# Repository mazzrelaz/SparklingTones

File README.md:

# SparklingTones

*Italiano · [English](README.en.md)*

App personale per controllare e organizzare i preset di un **Positive Grid Spark 2**
via Bluetooth, dal browser. Più un pedale ESP32 che fa lo stesso col piede.

**→ [mazzrelaz.github.io/SparklingTones](https://mazzrelaz.github.io/SparklingTones/)** · [guida all'uso](https://mazzrelaz.github.io/SparklingTones/guida.html)
(anche dentro l'app: menu ⋯ → Guida)

> **Progetto personale, in pausa.** È nato per risolvere un problema mio e funziona
> sul mio ampli. Il protocollo dello Spark 2 non è documentato da nessuna parte: qui
> è stato ricostruito osservando, misurando e verificando sull'hardware. Se stai
> cercando quello, la parte che ti serve è in [`docs/`](docs/) — vedi in fondo.

L'app è in italiano e in inglese (la lingua si sceglie nel pannello «Altro»). La
documentazione tecnica è in italiano, tranne il protocollo, che c'è anche
[in inglese](docs/protocollo-spark2.en.md).

---

## Cosa fa

**Organizza la libreria.** Lo Spark 2 tiene otto preset alla volta; l'app tiene tutti
quelli che vuoi, con nome, categorie, note e famiglia di suono, in un database nel
browser. Legge i preset dall'ampli, importa il `preset_backup.zip` dell'app ufficiale,
esporta e reimporta in JSON.

**Suona.** Una vista *Live* con banchi da otto pulsantoni grandi, pensata per essere
usata mentre si suona invece che per catalogare. Un preset già caricato sull'ampli si
attiva all'istante; uno che non c'è viene trasmesso per intero in circa un secondo.

**Regola.** Un editor della catena effetti che agisce **sul suono che sta suonando**:
le manopole si muovono e l'ampli risponde. Legge sempre lo stato vero dall'ampli prima
di aprirsi, perché la verità è lì e non nella libreria.

**Funziona senza rete.** È una PWA: installata, si apre e funziona anche offline —
a un concerto la rete non c'è.

## Cosa serve

Un browser con **Web Bluetooth**: Chrome o Edge su computer e Android.
**Su iPhone e iPad serve Bluefy** («Bluefy – Web BLE Browser» nell'App Store),
un browser gratuito che Web Bluetooth ce l'ha: Safari e gli altri no, perché su iOS ogni
browser è obbligato a usare il motore di Apple. Provato su iPhone e iPad: va tutto.
La libreria che sta in Safari non passa da sola in Bluefy: si esporta e si reimporta.

Niente altro. Niente account, niente server: la libreria sta nel tuo browser e non
esce di lì.

## Farlo girare

Non c'è niente da compilare e niente da installare.

```
git clone https://github.com/mazzrelaz/SparklingTones.git
```

Poi apri `index.html` con un doppio clic. Funziona da `file://` — per questo i moduli
sono classic script e non ES module.

Attenzione a una cosa: `file://` e `https://` sono **due origini diverse**, quindi due
database diversi. La libreria non passa dall'una all'altra da sola: si esporta in JSON
e si reimporta.

## Il pedale

In [`pedale/`](pedale/) c'è il firmware per un **ESP32-C3**: prende i banchi dall'app
via Bluetooth, se li tiene in memoria e poi è autonomo — si collega da solo all'ampli
e cambia preset col piede, senza telefono.

Verificato sull'hardware, su una schedina nuda senza saldature:

| | misurato |
|---|---|
| un preset intero, intervallo di connessione di sistema | 1246 ms |
| lo stesso, chiedendo 7,5 ms | **326 ms** |
| a regime | **178–215 ms** |

Il secondo che ci mette il telefono non è banda: sono sedici round-trip BLE. Web
Bluetooth non lascia toccare l'intervallo di connessione, NimBLE sull'ESP32 sì, ed è
tutta la differenza.

**Il firmware non serializza niente.** L'app produce i frame già pronti e il pedale
corregge un byte solo — il sequence number, che il checksum non copre. L'encoder resta
uno solo, in JavaScript, coperto dai test.

Il pedale è a metà: funziona su una devkit, l'hardware vero (cinque footswitch, due
tasti, LED, display) non è ancora stato costruito. `tools/pedale-sim.html` ne simula la
faccia in una pagina, con dentro la logica vera.

## Il protocollo — la parte utile a qualcun altro

Questa è probabilmente la ragione per cui sei qui. Tutto in
**[`docs/protocollo-spark2.md`](docs/protocollo-spark2.md)**, e le trappole più costose
sono riassunte in [`CLAUDE.md`](CLAUDE.md).

GATT: service `0xFFC0`, write `0xFFC1` (solo *write without response*), notify `0xFFC2`.
Messaggi `F0 01 <seq> <checksum> <cmd> <sub> <dati impacchettati> F7`, con i dati
codificati 7/8 bit e i float in big endian.

Quello che è costato di più scoprire:

- **I comandi sugli effetti vogliono un byte `0x00` in coda.** Senza, l'ampli risponde
  con un ack regolare e **non applica il comando**. Non è documentato da nessuna fonte,
  ed è una differenza dello Spark 2.
- **Chunk da 25 byte, non 128.** Con 128 lo Spark 2 si disconnette.
- **Tutti i chunk di un preset vanno con lo stesso sequence number**, altrimenti l'ampli
  li conferma tutti senza assemblarne nessuno.
- **`0x0127` non salva sullo Spark 2**, in nessuna delle forme provate.
- **Far suonare un preset e salvarlo in uno slot sono due strade diverse**, e la seconda
  vuole un giro via-e-ritorno che sembra decorazione e non lo è.
- **L'ack conferma la ricezione, non l'esecuzione.** E `writeWithoutResponse` fa sembrare
  riuscita ogni scrittura: l'assenza di errori non è una verifica.

Il looper si comanda (`0x0175`), tranne la battuta di conteggio col click: quella è
un'indagine chiusa, e tutto ciò che è stato escluso sta in
[`docs/looper.md`](docs/looper.md), così nessuno ripercorre sette strade già chiuse.

Le catture grezze dall'ampli sono in [`captures/`](captures/).

## Test

Aprire le pagine in `test/`. Girano contro catture reali dell'ampli, quindi
intercettano una regressione nella codifica senza avere l'hardware a portata.

| | |
|---|---|
| `protocol-test.html` | 125 test — encoder e decoder, round-trip byte per byte |
| `transport-test.html` | 48 test — coda di invio e riassemblaggio |
| `store-test.html` | 99 test — libreria, banchi, categorie |
| `backup-test.html` | 33 test — lettura dello zip dell'app ufficiale |

## Avvertenze

**Scrivere in uno slot dell'ampli non si torna indietro.** Quello che c'era prima è
perso.

**L'ampli si può piantare**, e allora serve staccare la corrente. Succede coi comandi
pesanti — ricostruire un blocco DSP, o girare le manopole più in fretta di quanto la
radio riesca a portare.

**L'elenco dei modelli di effetto non è verificato**: viene da un catalogo di terzi, e
chiedere all'ampli un modello che non ha è uno dei modi per piantarlo. L'app distingue
quelli che ha visto uscire dal tuo ampli da quelli solo supposti.

**Provato su un solo Spark 2.** Con un altro esemplare, o un altro firmware, non so
cosa succede.

## Licenza e riconoscimenti

MIT, Massimo Togni. Vedi [`LICENSE`](LICENSE) e [`NOTICE`](NOTICE).

- I nomi di effetti e manopole vengono dal catalogo di
  **[Soundshed](https://github.com/soundshed/soundshed-app)** (MIT).
- Il riferimento per il protocollo BLE è
  **[paulhamsh/Spark](https://github.com/paulhamsh/Spark)** (Apache 2.0), i cui sorgenti
  stanno in [`reference/`](reference/).
- **[Ignitron](https://github.com/stangreg/Ignitron)** di stangreg è un pedale ESP32 per
  lo Spark, ed è da lì che vengono i comandi del looper.

**Nessun rapporto con Positive Grid Inc.** Non è un prodotto ufficiale, non è approvato
né supportato, e non usa loro codice. «Spark» e «Positive Grid» sono citati solo per
dire con cosa funziona.

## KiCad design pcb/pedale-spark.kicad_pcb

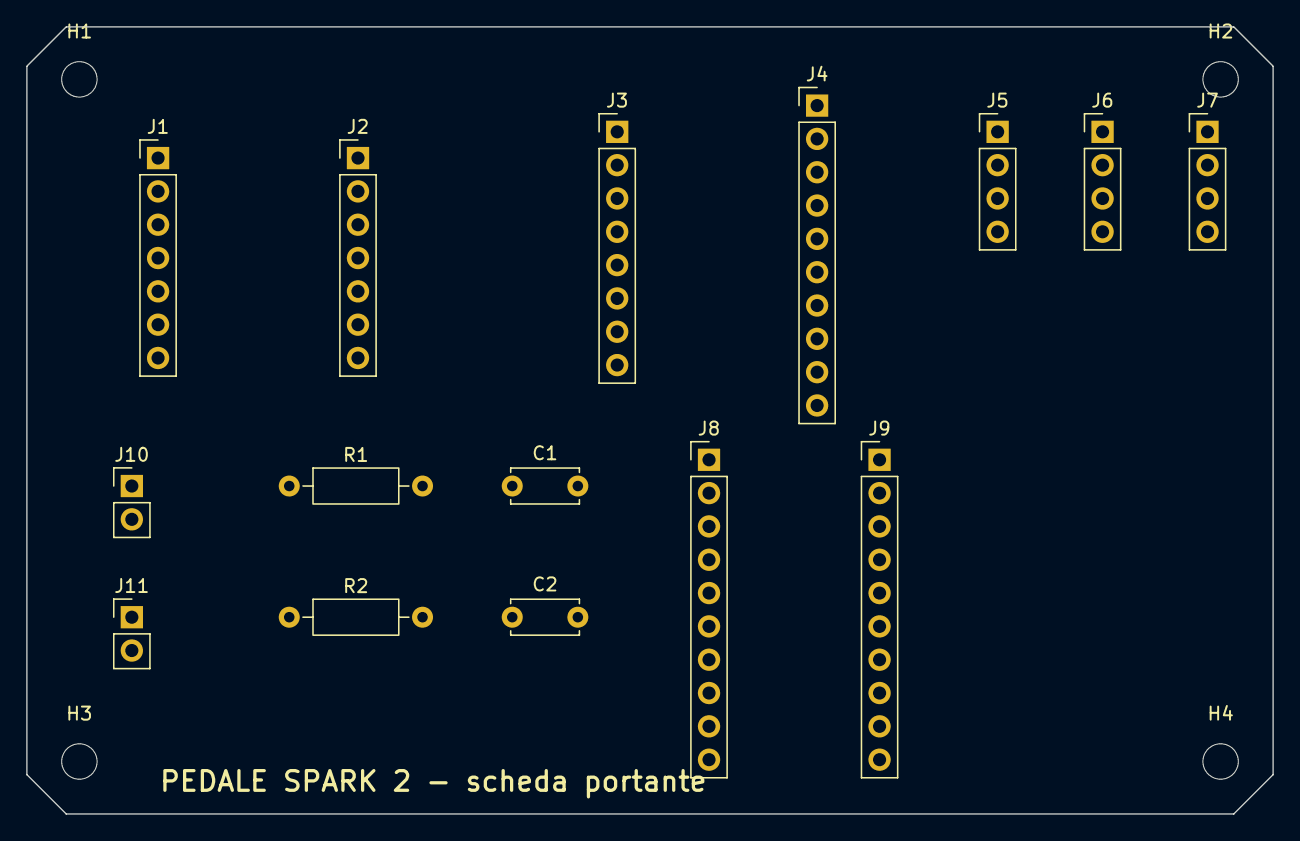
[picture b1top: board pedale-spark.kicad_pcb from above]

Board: 2 copper layers, 95.0 x 60.0 mm, 19 parts (0 on the bottom side), 23 nets, no tracks yet.

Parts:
C1: 470n; C_Disc_D5.0mm_W2.5mm_P5.00mm
C2: 47n; C_Disc_D5.0mm_W2.5mm_P5.00mm
H1, H2, H3, H4: M2.5; MountingHole_2.7mm_M2.5
J1: XIAO S3 fila A; PinHeader_1x07_P2.54mm_Vertical
J2: XIAO S3 fila B; PinHeader_1x07_P2.54mm_Vertical
J3: MCP23017 controllo; PinHeader_1x08_P2.54mm_Vertical
J4: MCP23017 port A; PinHeader_1x10_P2.54mm_Vertical
J5: MCP PB0-PB3; PinHeader_1x04_P2.54mm_Vertical
J6: MCP PB4-PB7; PinHeader_1x04_P2.54mm_Vertical
J7: al display; PinHeader_1x04_P2.54mm_Vertical
J8: ai 7 pulsanti; PinHeader_1x10_P2.54mm_Vertical
J9: agli 8 LED; PinHeader_1x10_P2.54mm_Vertical
J10: dalla cella; PinHeader_1x02_P2.54mm_Vertical
J11: a BAT+/BAT- XIAO; PinHeader_1x02_P2.54mm_Vertical
R1, R2: 200k; R_Axial_DIN0207_L6.3mm_D2.5mm_P10.16mm_Horizontal

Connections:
+3V3: C2.1, J2.3, J3.4, J3.6, J7.1
D3_INTA: J1.4, J3.3
GND: C1.2, C2.2, J2.2, J3.1, J3.2, J3.5, J4.1, J4.10, J7.2, J8.1, J8.10, J9.1, J9.10, J10.2, J11.2, R2.2
PA0: J4.2, J8.2
PA1: J4.3, J8.3
PA2: J4.4, J8.4
PA3: J4.5, J8.5
PA4: J4.6, J8.6
PA5: J4.7, J8.7
PA6: J4.8, J8.8
PA7: J4.9, J8.9
PB0: J5.1, J9.2
PB1: J5.2, J9.3
PB2: J5.3, J9.4
PB3: J5.4, J9.5
PB4: J6.1, J9.6
PB5: J6.2, J9.7
PB6: J6.3, J9.8
PB7: J6.4, J9.9
SCL: J1.6, J3.8, J7.3
SDA: J1.5, J3.7, J7.4
VBAT: J10.1, J11.1, R1.1
VSENSE: C1.1, J1.1, R1.2, R2.1

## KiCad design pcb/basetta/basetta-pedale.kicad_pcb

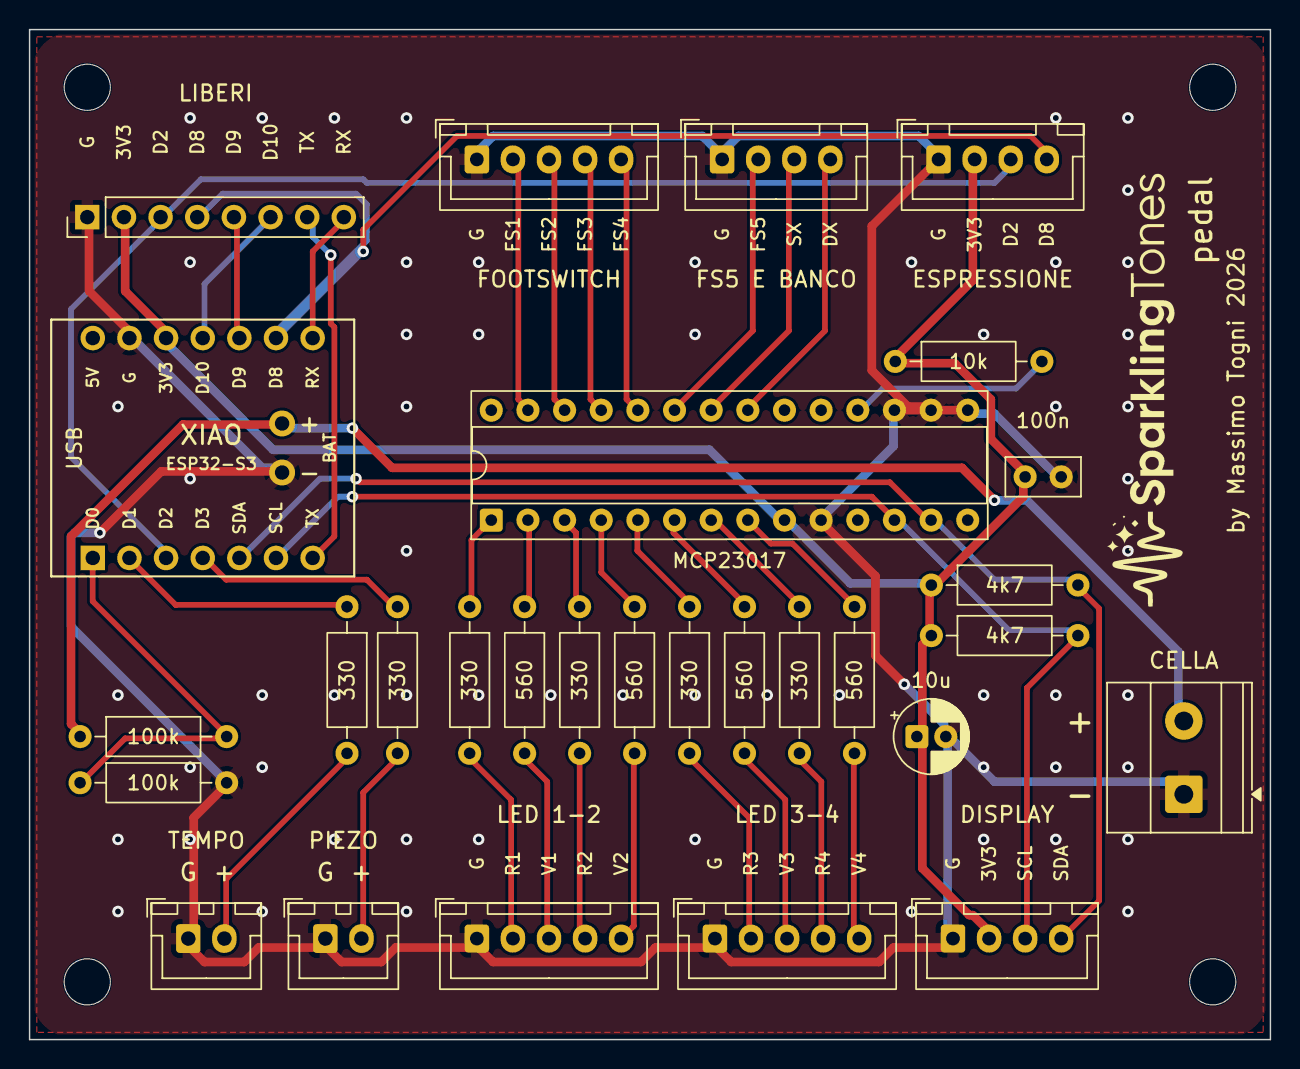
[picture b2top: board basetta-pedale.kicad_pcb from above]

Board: 2 copper layers, 86.0 x 70.0 mm, 34 parts (0 on the bottom side), 40 nets.

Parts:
C1: 100n; C_Disc_D5.0mm_W2.5mm_P2.50mm
C2: 10u; CP_Radial_D5.0mm_P2.00mm
H1, H2, H3, H4: MountingHole_3.2mm_M3
J1: J1; JST_XH_B5B-XH-A_1x05_P2.50mm_Vertical
J2: J2; JST_XH_B4B-XH-A_1x04_P2.50mm_Vertical
J3: J3; JST_XH_B5B-XH-A_1x05_P2.50mm_Vertical
J4: J4; JST_XH_B5B-XH-A_1x05_P2.50mm_Vertical
J5: J5; JST_XH_B4B-XH-A_1x04_P2.50mm_Vertical
J6: J6; JST_XH_B2B-XH-A_1x02_P2.50mm_Vertical
J7: J7; JST_XH_B2B-XH-A_1x02_P2.50mm_Vertical
J8: BAT
J9: J9; TerminalBlock_Phoenix_MKDS-1,5-2-5.08_1x02_P5.08mm_Horizont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
J10: J10; PinHeader_1x08_P2.54mm_Vertical
J11: J11; JST_XH_B4B-XH-A_1x04_P2.50mm_Vertical
R1, R2: 4k7; R_Axial_DIN0207_L6.3mm_D2.5mm_P10.16mm_Horizontal
R3: 10k; R_Axial_DIN0207_L6.3mm_D2.5mm_P10.16mm_Horizontal
R4, R5: 100k; R_Axial_DIN0207_L6.3mm_D2.5mm_P10.16mm_Horizontal
R6, R7, R8, R10, R12, R14: 330; R_Axial_DIN0207_L6.3mm_D2.5mm_P10.16mm_Horizontal
R9, R11, R13, R15: 560; R_Axial_DIN0207_L6.3mm_D2.5mm_P10.16mm_Horizontal
U1: XIAO ESP32-S3
U2: MCP23017; DIP-28_W7.62mm_Socket

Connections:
+3V3: C1.1, C2.1, J5.2, J10.2, J11.2, R1.1, R2.1, R3.1, U1.12, U2.9
CLIC: R7.1, U1.4
CLIC_R: J7.2, R7.2
D2: J10.3, J11.3, U1.3
D8: J10.4, J11.4, U1.9
D9: J10.5, U1.10
D10: J10.6, U1.11
GND: C1.2, C2.2, J1.1, J2.1, J3.1, J4.1, J5.1, J6.1, J7.1, J8.1, J9.1, J10.1, J11.1, R5.2, U1.13, U2.10, U2.15, U2.16, U2.17
LED_T: R6.1, U1.2
LED_T_R: J6.2, R6.2
LR1: J3.2, R8.2
LR2: J3.4, R10.2
LR3: J4.2, R12.2
LR4: J4.4, R14.2
LV1: J3.3, R9.2
LV2: J3.5, R11.2
LV3: J4.3, R13.2
LV4: J4.5, R15.2
PA0: J2.4, U2.21
PA1: J2.3, U2.22
PA2: J2.2, U2.23
PA3: J1.5, U2.24
PA4: J1.4, U2.25
PA5: J1.3, U2.26
PA6: J1.2, U2.27
PB0: R8.1, U2.1
PB1: R9.1, U2.2
PB2: R10.1, U2.3
PB3: R11.1, U2.4
PB4: R12.1, U2.5
PB5: R13.1, U2.6
PB6: R14.1, U2.7
PB7: R15.1, U2.8
RESET: R3.2, U2.18
RX: J10.8, U1.8
SCL: J5.3, R2.2, U1.6, U2.12
SDA: J5.4, R1.2, U1.5, U2.13
TX: J10.7, U1.7
VBAT: J8.2, J9.2, R4.1
VSENSE: R4.2, R5.1, U1.1

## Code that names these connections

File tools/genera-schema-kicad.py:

# -*- coding: utf-8 -*-
"""Genera lo schema elettrico della scheda portante del pedale, per KiCad 10.

Lo stile e' quello dei connettori: niente fili fra un pin e l'altro, ma
un'etichetta di rete su ogni pin. Su una scheda che e' quasi tutta zoccoli e
connettori si legge meglio, e soprattutto e' generabile senza sbagliare.
"""
import os
import re
import uuid

KICAD = r"C:\Program Files\KiCad\10.0\share\kicad\symbols"
FUORI = os.environ["SCRATCH"]

# ----------------------------------------------------------- le librerie --


def leggi(percorso):
    with open(percorso, encoding="utf-8") as f:
        return f.read()


def estrai_simbolo(testo, nome):
    """Ritaglia il blocco (symbol "nome" ...) contando le parentesi."""
    ago = '(symbol "%s"' % nome
    i = testo.find(ago)
    if i < 0:
        raise SystemExit("simbolo non trovato: " + nome)
    liv = 0
    j = i
    in_str = False
    while j < len(testo):
        c = testo[j]
        if c == '"' and testo[j - 1] != "\\":
            in_str = not in_str
        elif not in_str:
            if c == "(":
                liv += 1
            elif c == ")":
                liv -= 1
                if liv == 0:
                    return testo[i:j + 1]
        j += 1
    raise SystemExit("blocco non chiuso: " + nome)


def pin_del_simbolo(blocco):
    """{numero: (x, y)} — l'`at` di un pin e' il suo punto di connessione."""
    fuori = {}
    for m in re.finditer(
            r"\(pin\s+\w+\s+\w+\s*\(at\s+([-\d.]+)\s+([-\d.]+)\s+[-\d.]+\)"
            r".*?\(number\s+\"([^\"]+)\"", blocco, re.S):
        x, y, n = float(m.group(1)), float(m.group(2)), m.group(3)
        fuori[n] = (x, y)
    return fuori


LIB = {
    "Connector_Generic": leggi(os.path.join(KICAD, "Connector_Generic.kicad_sym")),
    "Device": leggi(os.path.join(KICAD, "Device.kicad_sym")),
}

# --------------------------------------------------------- i componenti --
# (riferimento, libreria, simbolo, valore, x, y, {pin: rete})

def conn(n):
    return "Conn_01x%02d" % n


PEZZI = [
    # Tutte le etichette vanno a SINISTRA: questi connettori hanno i pin solo
    # da quel lato, e mettendole a destra finirebbero sopra il simbolo.
    # Le colonne sono spaziate 70 mm, che e' quanto serve al testo per stare
    # comodo alla sinistra del suo connettore.

    # --- colonna 1: XIAO fila A, batteria, partitore ---------------------
    ("J1", "Connector_Generic", conn(7), "XIAO S3 - fila A", 60, 50, {
        "1": "VSENSE", "2": "D1", "3": "D2", "4": "D3_INTA",
        "5": "SDA", "6": "SCL", "7": "D6_TX"}),
    ("J10", "Connector_Generic", conn(2), "dalla cella", 60, 125, {
        "1": "VBAT", "2": "GND"}),
    ("J11", "Connector_Generic", conn(2), "fili a BAT+/BAT- della XIAO", 60, 150, {
        "1": "VBAT", "2": "GND"}),
    ("R1", "Device", "R", "200k", 60, 185, {"1": "VBAT", "2": "VSENSE"}),
    ("R2", "Device", "R", "200k", 60, 210, {"1": "VSENSE", "2": "GND"}),

    # --- colonna 2: XIAO fila B, condensatori ----------------------------
    ("J2", "Connector_Generic", conn(7), "XIAO S3 - fila B", 130, 50, {
        "1": "+5V_NC", "2": "GND", "3": "+3V3", "4": "D10",
        "5": "D9", "6": "D8", "7": "D7_RX"}),
    ("C1", "Device", "C", "470n - filtro lettura batteria", 130, 185, {
        "1": "VSENSE", "2": "GND"}),
    ("C2", "Device", "C", "47n - disaccoppiamento espansore", 130, 210, {
        "1": "+3V3", "2": "GND"}),

    # --- colonna 3: espansore --------------------------------------------
    ("J3", "Connector_Generic", conn(8), "MCP23017 - fila di controllo", 200, 50, {
        "1": "GND", "2": "GND", "3": "D3_INTA", "4": "+3V3",
        "5": "GND", "6": "+3V3", "7": "SDA", "8": "SCL"}),
    ("J4", "Connector_Generic", conn(10), "MCP23017 - port A", 200, 120, {
        "1": "GND", "2": "PA0", "3": "PA1", "4": "PA2", "5": "PA3",
        "6": "PA4", "7": "PA5", "8": "PA6", "9": "PA7", "10": "GND"}),

    # --- colonna 4: lati corti dell'espansore e display -------------------
    ("J5", "Connector_Generic", conn(4), "MCP23017 - PB0..PB3", 270, 50, {
        "1": "PB0", "2": "PB1", "3": "PB2", "4": "PB3"}),
    ("J6", "Connector_Generic", conn(4), "MCP23017 - PB4..PB7", 270, 90, {
        "1": "PB4", "2": "PB5", "3": "PB6", "4": "PB7"}),
    ("J7", "Connector_Generic", conn(4), "al display", 270, 130, {
        "1": "+3V3", "2": "GND", "3": "SCL", "4": "SDA"}),

    # --- colonna 5: verso il coperchio -----------------------------------
    ("J8", "Connector_Generic", conn(10), "ai 7 pulsanti", 340, 50, {
        "1": "GND", "2": "PA0", "3": "PA1", "4": "PA2", "5": "PA3",
        "6": "PA4", "7": "PA5", "8": "PA6", "9": "PA7", "10": "GND"}),
    ("J9", "Connector_Generic", conn(10), "agli 8 LED", 340, 130, {
        "1": "GND", "2": "PB0", "3": "PB1", "4": "PB2", "5": "PB3",
        "6": "PB4", "7": "PB5", "8": "PB6", "9": "PB7", "10": "GND"}),
]

# ------------------------------------------------------------ scrittura --

usati = []
for _, lib, sim, *_ in PEZZI:
    if (lib, sim) not in usati:
        usati.append((lib, sim))

blocchi = []
pin_di = {}
for lib, sim in usati:
    b = estrai_simbolo(LIB[lib], sim)
    pin_di[(lib, sim)] = pin_del_simbolo(b)
    b = b.replace('(symbol "%s"' % sim, '(symbol "%s:%s"' % (lib, sim), 1)
    blocchi.append(b)

PROG = "pedale-spark"
righe = []
a = righe.append
a("(kicad_sch")
a('\t(version 20250610)')
a('\t(generator "eeschema")')
a('\t(generator_version "10.0")')
a('\t(uuid "%s")' % uuid.uuid4())
a('\t(paper "A3")')
a('\t(title_block')
a('\t\t(title "Pedale Spark 2 - scheda portante")')
a('\t\t(rev "bozza")')
a('\t\t(comment 1 "Zoccoli per XIAO S3 e MCP23017, connettori verso il coperchio")')
a('\t)')
a('\t(lib_symbols')
for b in blocchi:
    a(b)
a('\t)')

for rif, lib, sim, val, x, y, reti in PEZZI:
    u = str(uuid.uuid4())
    a('\t(symbol')
    a('\t\t(lib_id "%s:%s")' % (lib, sim))
    a('\t\t(at %g %g 0)' % (x, y))
    a('\t\t(unit 1)')
    a('\t\t(exclude_from_sim no)(in_bom yes)(on_board yes)(dnp no)')
    a('\t\t(uuid "%s")' % u)
    alto = max(v[1] for v in pin_di[(lib, sim)].values())
    a('\t\t(property "Reference" "%s" (at %g %g 0)'
      '(effects (font (size 1.27 1.27) (bold yes)) (justify left)))' % (rif, x - 2.54, y - alto - 8))
    a('\t\t(property "Value" "%s" (at %g %g 0)'
      '(effects (font (size 1.27 1.27)) (justify left)))' % (val, x - 2.54, y - alto - 5.2))
    for n in sorted(pin_di[(lib, sim)], key=lambda s: int(s)):
        a('\t\t(pin "%s" (uuid "%s"))' % (n, uuid.uuid4()))
    a('\t\t(instances (project "%s" (path "/%s" (reference "%s") (unit 1))))'
      % (PROG, u, rif))
    a('\t)')

    px = pin_di[(lib, sim)]
    for n, rete in reti.items():
        if n not in px:
            raise SystemExit("%s: pin %s inesistente" % (rif, n))
        ax = x + px[n][0]
        ay = y - px[n][1]
        giust = "right"
        rot = 180
        a('\t(label "%s" (at %g %g %d)'
          '(effects (font (size 1.27 1.27)) (justify %s bottom))'
          '(uuid "%s"))' % (rete, ax, ay, rot, giust, uuid.uuid4()))

a(')')

os.makedirs(FUORI, exist_ok=True)
with open(os.path.join(FUORI, PROG + ".kicad_sch"), "w", encoding="utf-8") as f:
    f.write("\n".join(righe) + "\n")

with open(os.path.join(FUORI, PROG + ".kicad_pro"), "w", encoding="utf-8") as f:
    f.write('{\n  "board": {},\n  "meta": {"filename": "%s.kicad_pro", '
            '"version": 3},\n  "sheets": [],\n  "text_variables": {}\n}\n' % PROG)

print("scritto:", os.path.join(FUORI, PROG + ".kicad_sch"))
print("componenti:", len(PEZZI))
reti_tutte = sorted({r for *_, reti in PEZZI for r in reti.values()})
print("reti (%d): %s" % (len(reti_tutte), ", ".join(reti_tutte)))
